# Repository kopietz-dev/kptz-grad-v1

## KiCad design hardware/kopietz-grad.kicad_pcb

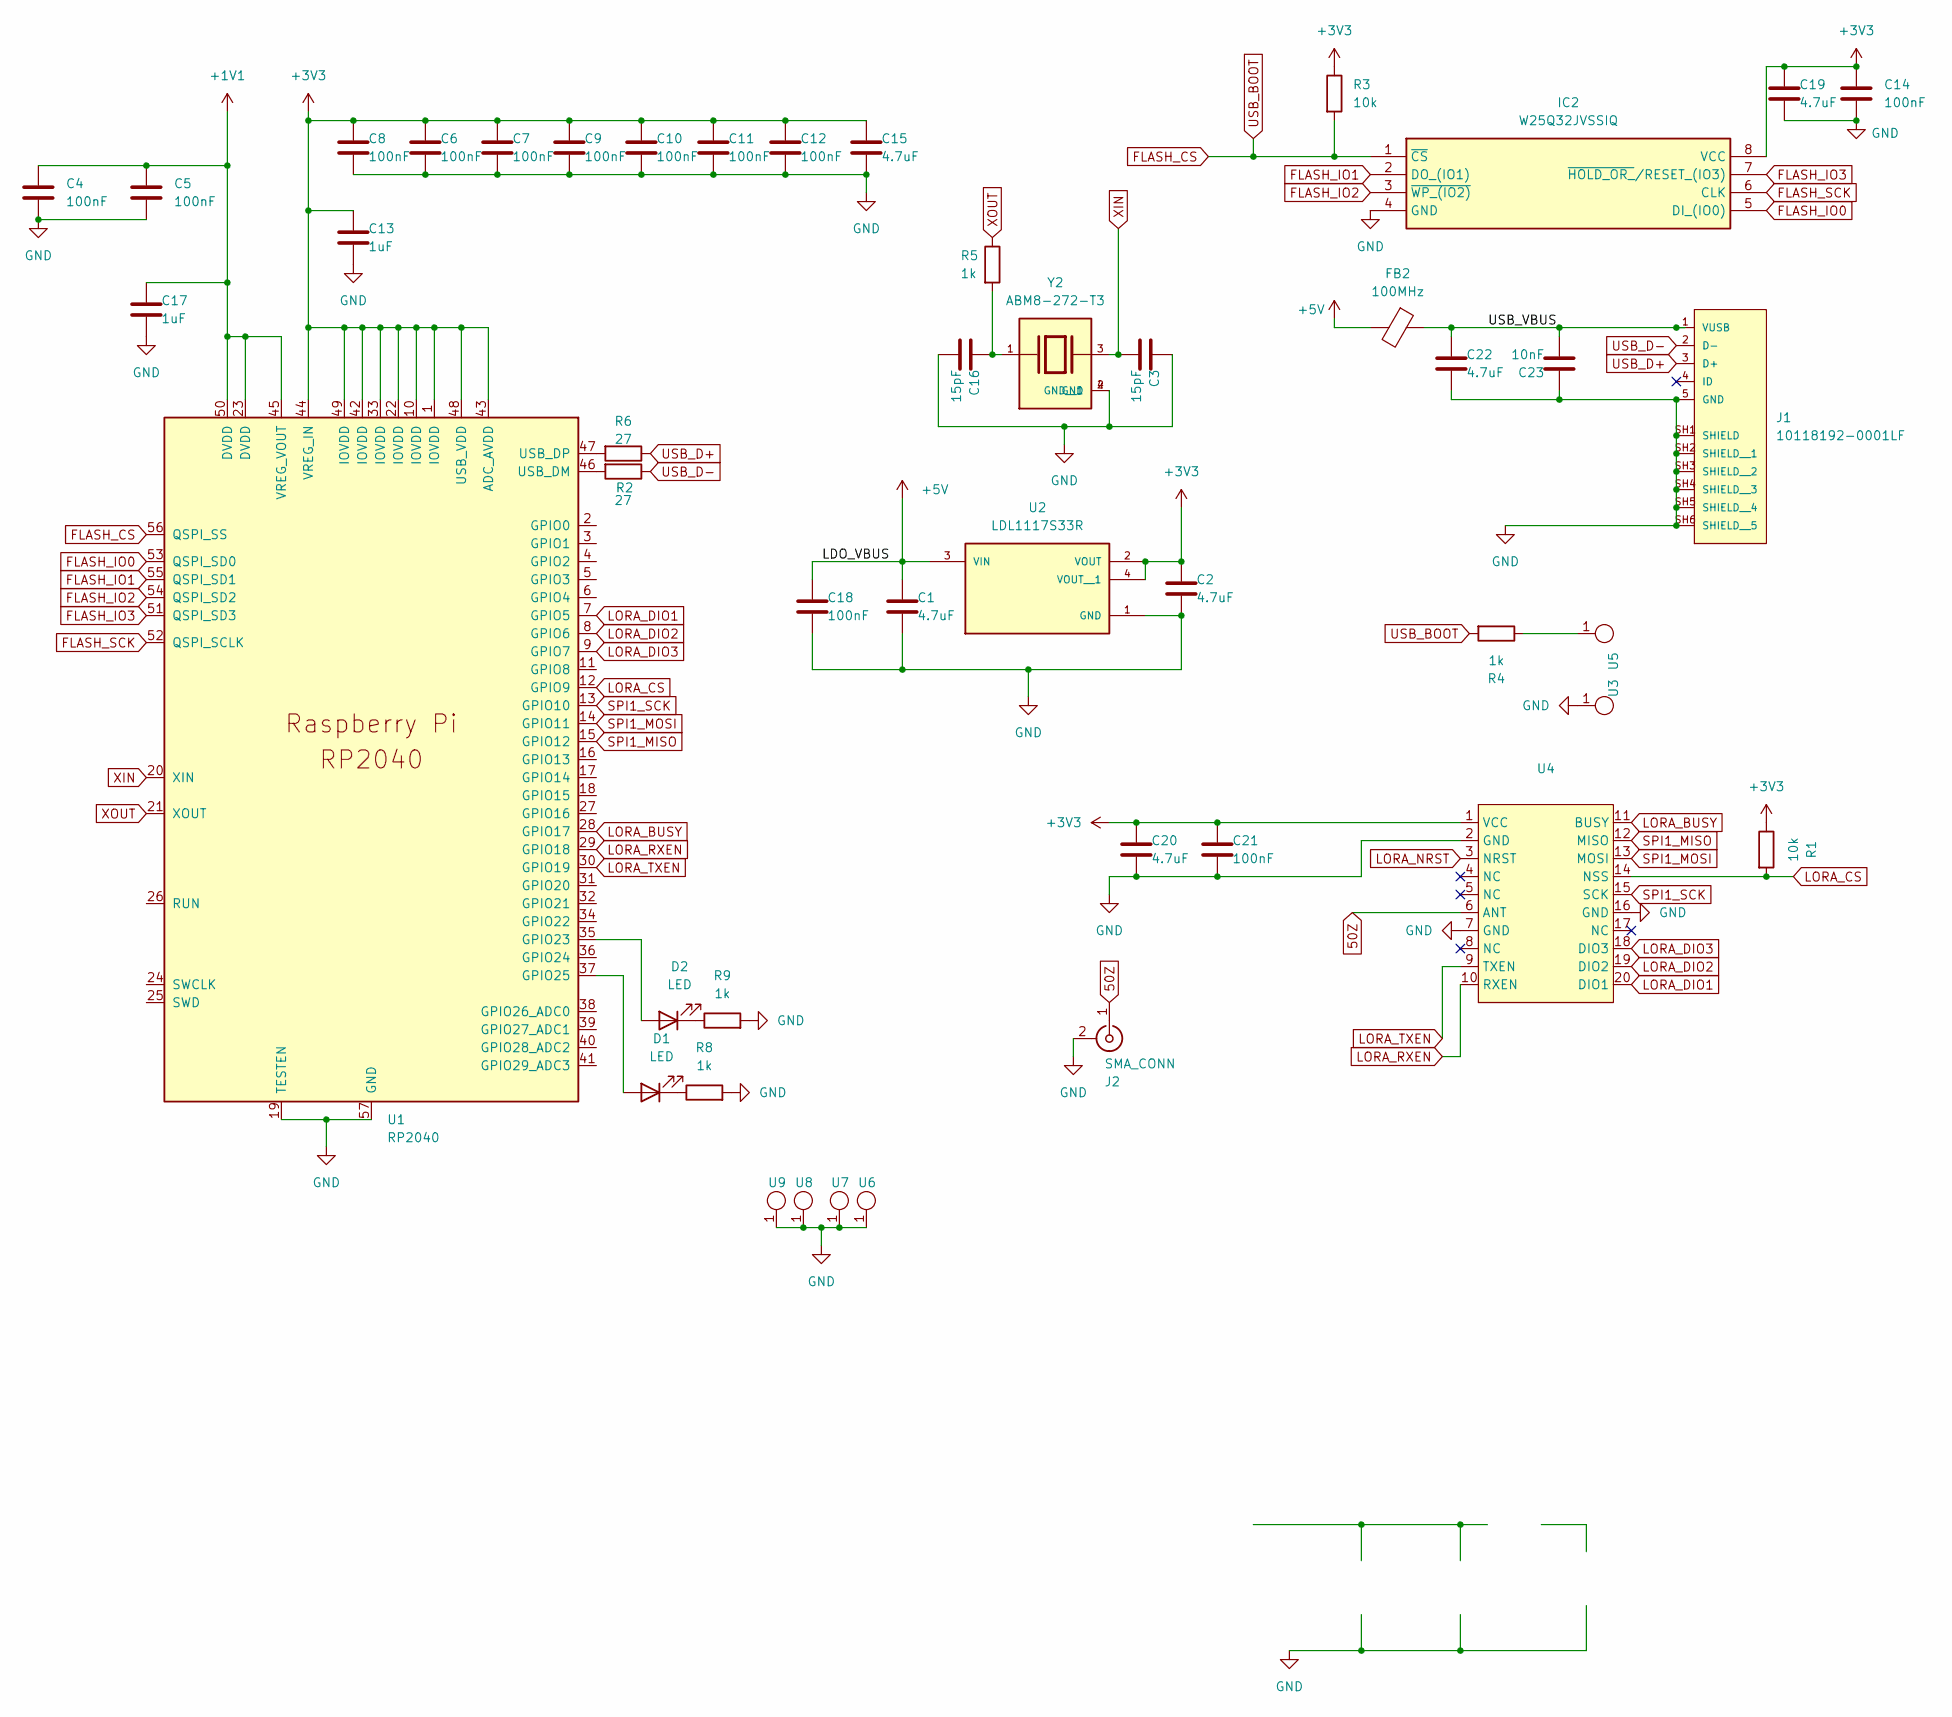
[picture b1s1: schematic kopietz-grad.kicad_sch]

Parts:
C1, C2, C15, C19, C20, C22: 4.7uF; C_0402_1005Metric
C3, C16: 15pF; C_0402_1005Metric
C4, C5, C6, C7, C8, C9, C10, C11, C12, C14, C18, C21: 100nF; C_0402_1005Metric
C13, C17: 1uF; C_0402_1005Metric
C23: 10nF; C_0402_1005Metric
D1, D2: LED; D_0603_1608Metric
FB2: 100MHz; L_0805_2012Metric
IC2: W25Q32JVSSIQ; SOIC127P790X216-8N; Manufacturer_Part_Number W25Q32JVSSIQ; Mouser Part Number 454-W25Q32JVSSIQ
J1: 10118192-0001LF; AMPHENOL_10118192-0001LF; PARTREV B
J2: SMA_CONN; SMA_Samtec_SMA-J-P-H-ST-EM1_EdgeMount
R1, R3: 10k; R_0402_1005Metric
R2, R6: 27; R_0402_1005Metric
R4, R5: 1k; R_0402_1005Metric
R8, R9: 1k; R_0603_1608Metric_Pad0.98x0.95mm_HandSolder
U1: RP2040; RP2040-QFN-56
U2: LDL1117S33R; SOT230P700X180-4N; PARTREV 7
U3, U5: OUTPAD
U4: E220-400MM22S
U6, U7, U8, U9: MountingHole_3.2mm_M3_DIN965_Pad
Y2: ABM8-272-T3; XTAL_ABM8-272-T3; PARTREV 07-29-20

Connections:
50Z: J2.1 (In), U4.6 (ANT)
+1V1: C4.1, C5.1, C17.1, U1.23 (DVDD), U1.45 (VREG_VOUT), U1.50 (DVDD)
+3V3: C2.1, C6.1, C7.1, C8.1, C9.1, C10.1, C11.1, C12.1, C13.1, C14.1, C15.1, C19.1, C20.1, C21.1, IC2.8 (VCC), R1.1, R3.1, U1.1 (IOVDD), U1.10 (IOVDD), U1.22 (IOVDD), U1.33 (IOVDD), U1.42 (IOVDD), U1.43 (ADC_AVDD), U1.44 (VREG_IN), U1.48 (USB_VDD), U1.49 (IOVDD), U2.2 (VOUT), U2.4 (VOUT__1), U4.1 (VCC); also elsewhere on the board
+5V: C1.1, C18.1, FB2.2, U2.3 (VIN)
/USB_VBUS: C22.1, C23.2, FB2.1, J1.1 (VUSB)
FLASH_CS: IC2.1 (~CS), R3.2, R4.2, U1.56 (QSPI_SS)
FLASH_IO0: IC2.5 (DI_(IO0)), U1.53 (QSPI_SD0)
FLASH_IO1: IC2.2 (DO_(IO1)), U1.55 (QSPI_SD1)
FLASH_IO2: IC2.3 (~WP_(IO2)), U1.54 (QSPI_SD2)
FLASH_IO3: IC2.7 (~HOLD_OR_/RESET_(IO3)), U1.51 (QSPI_SD3)
FLASH_SCK: IC2.6 (CLK), U1.52 (QSPI_SCLK)
GND: C1.2, C2.2, C3.1, C4.2, C5.2, C6.2, C7.2, C8.2, C9.2, C10.2, C11.2, C12.2, C13.2, C14.2, C15.2, C16.2, C17.2, C18.2, C19.2, C20.2, C21.2, C22.2, C23.1, IC2.4 (GND), J1.5 (GND), J1.SH1 (SHIELD), J1.SH2 (SHIELD__1), J1.SH3 (SHIELD__2), J1.SH4 (SHIELD__3), J1.SH5 (SHIELD__4), J1.SH6 (SHIELD__5), J2.2 (Ext), R8.2, R9.2, U1.19 (TESTEN), U1.57 (GND), U2.1 (GND), U3.1, U4.2 (GND), U4.7 (GND), U4.16 (GND), U6.1, U7.1, U8.1, U9.1, Y2.2 (GND), Y2.4 (GND__1); also elsewhere on the board
LORA_BUSY: U1.28 (GPIO17), U4.11 (BUSY)
LORA_CS: R1.2, U1.12 (GPIO9), U4.14 (NSS)
LORA_DIO1: U1.7 (GPIO5), U4.20 (DIO1)
LORA_DIO2: U1.8 (GPIO6), U4.19 (DIO2)
LORA_DIO3: U1.9 (GPIO7), U4.18 (DIO3)
LORA_NRST: U4.3 (NRST)
LORA_RXEN: U1.29 (GPIO18), U4.10 (RXEN)
LORA_TXEN: U1.30 (GPIO19), U4.9 (TXEN)
unnamed: C16.1, R5.2, Y2.1
unnamed: D1.2 (A), U1.37 (GPIO25)
unnamed: D1.1 (K), R8.1
unnamed: D2.2 (A), U1.35 (GPIO23)
unnamed: D2.1 (K), R9.1
unnamed: R4.1, U5.1
unnamed: R2.2, U1.46 (USB_DM)
unnamed: R6.2, U1.47 (USB_DP)
SPI1_MISO: U1.15 (GPIO12), U4.12 (MISO)
SPI1_MOSI: U1.14 (GPIO11), U4.13 (MOSI)
SPI1_SCK: U1.13 (GPIO10), U4.15 (SCK)
USB_D+: J1.3 (D+), R6.1
USB_D-: J1.2 (D-), R2.1
XIN: C3.2, U1.20 (XIN), Y2.3
XOUT: R5.1, U1.21 (XOUT)

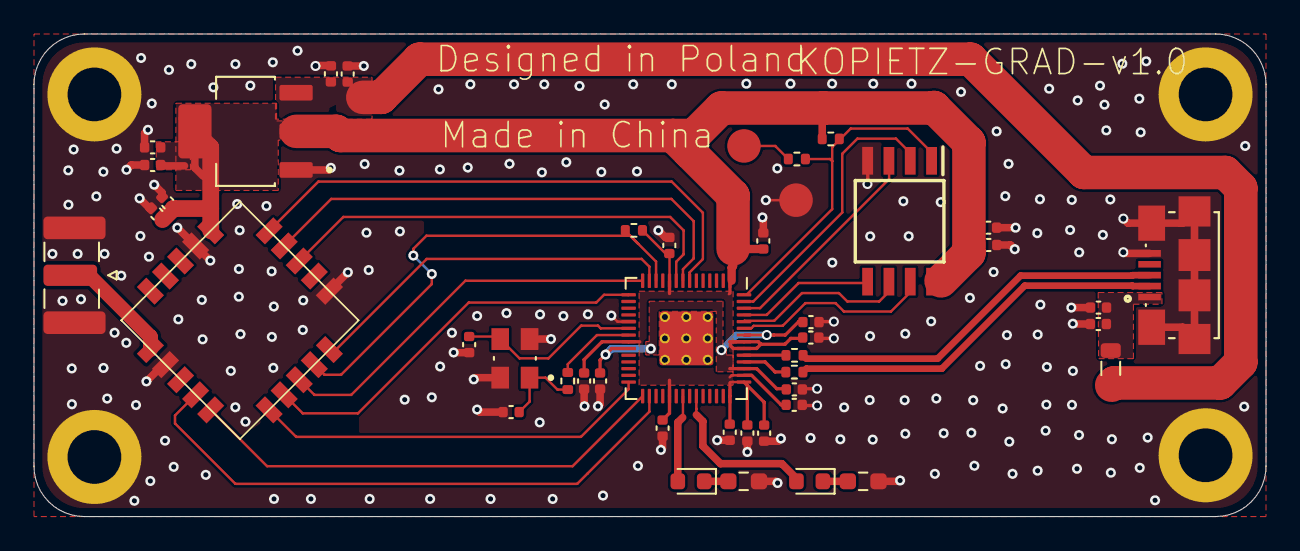
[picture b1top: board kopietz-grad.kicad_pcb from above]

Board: 2 copper layers, 73.4 x 28.8 mm, 48 parts (0 on the bottom side), 34 nets.

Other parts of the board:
C20#2: 4.7uF; C_0402_1005Metric

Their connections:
+3V3: C20#2.2; also elsewhere on the board
GND: C20#2.1; also elsewhere on the board
